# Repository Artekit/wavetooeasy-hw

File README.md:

# Artekit WaveTooEasy - Hardware files

This repository contains the Eagle files and mechanical drawings for the [Artekit WaveTooEasy](https://www.artekit.eu/products/devboards/wavetooeasy/) board.

## Links

* [WaveTooEasy product page](https://www.artekit.eu/products/devboards/wavetooeasy/)
* [WaveTooEasy manual](https://www.artekit.eu/doc/guides/wavetooeasy/)
* [WaveTooEasy - Library for Arduino](https://github.com/Artekit/Artekit_WaveTooEasy)
* [WaveTooEasy - Generic C library](https://github.com/Artekit/wavetooeasy-c-lib)

## Bugs report

You can report bugs here by creating a new issue or in the [Artekit forum](https://forum.artekit.eu/).

## License

Attribution-ShareAlike 3.0 Unported (CC BY-SA 3.0)

Copyright (c) 2021 Artekit Labs.

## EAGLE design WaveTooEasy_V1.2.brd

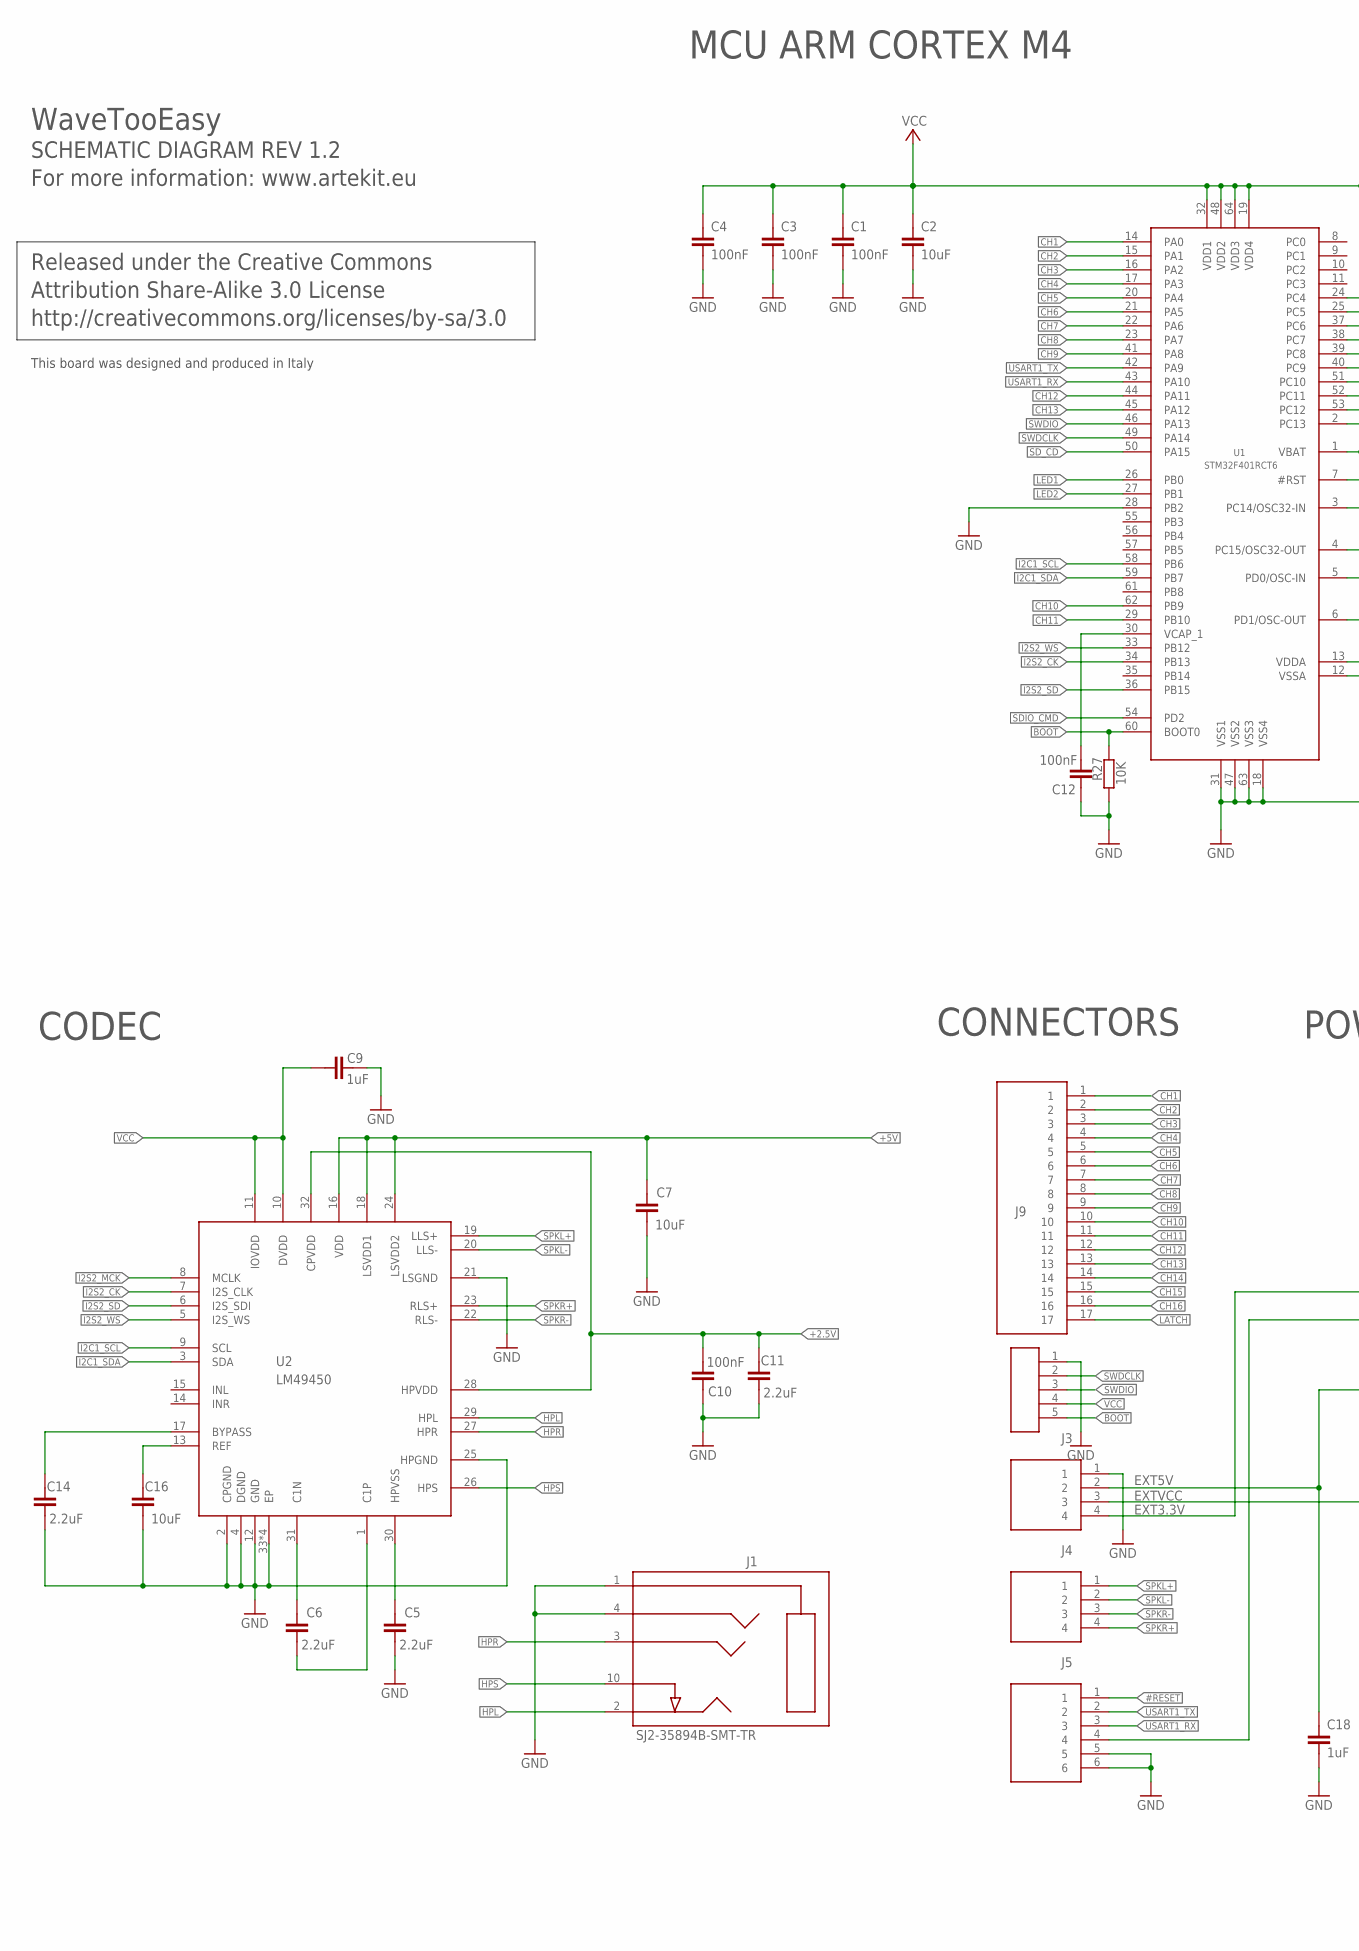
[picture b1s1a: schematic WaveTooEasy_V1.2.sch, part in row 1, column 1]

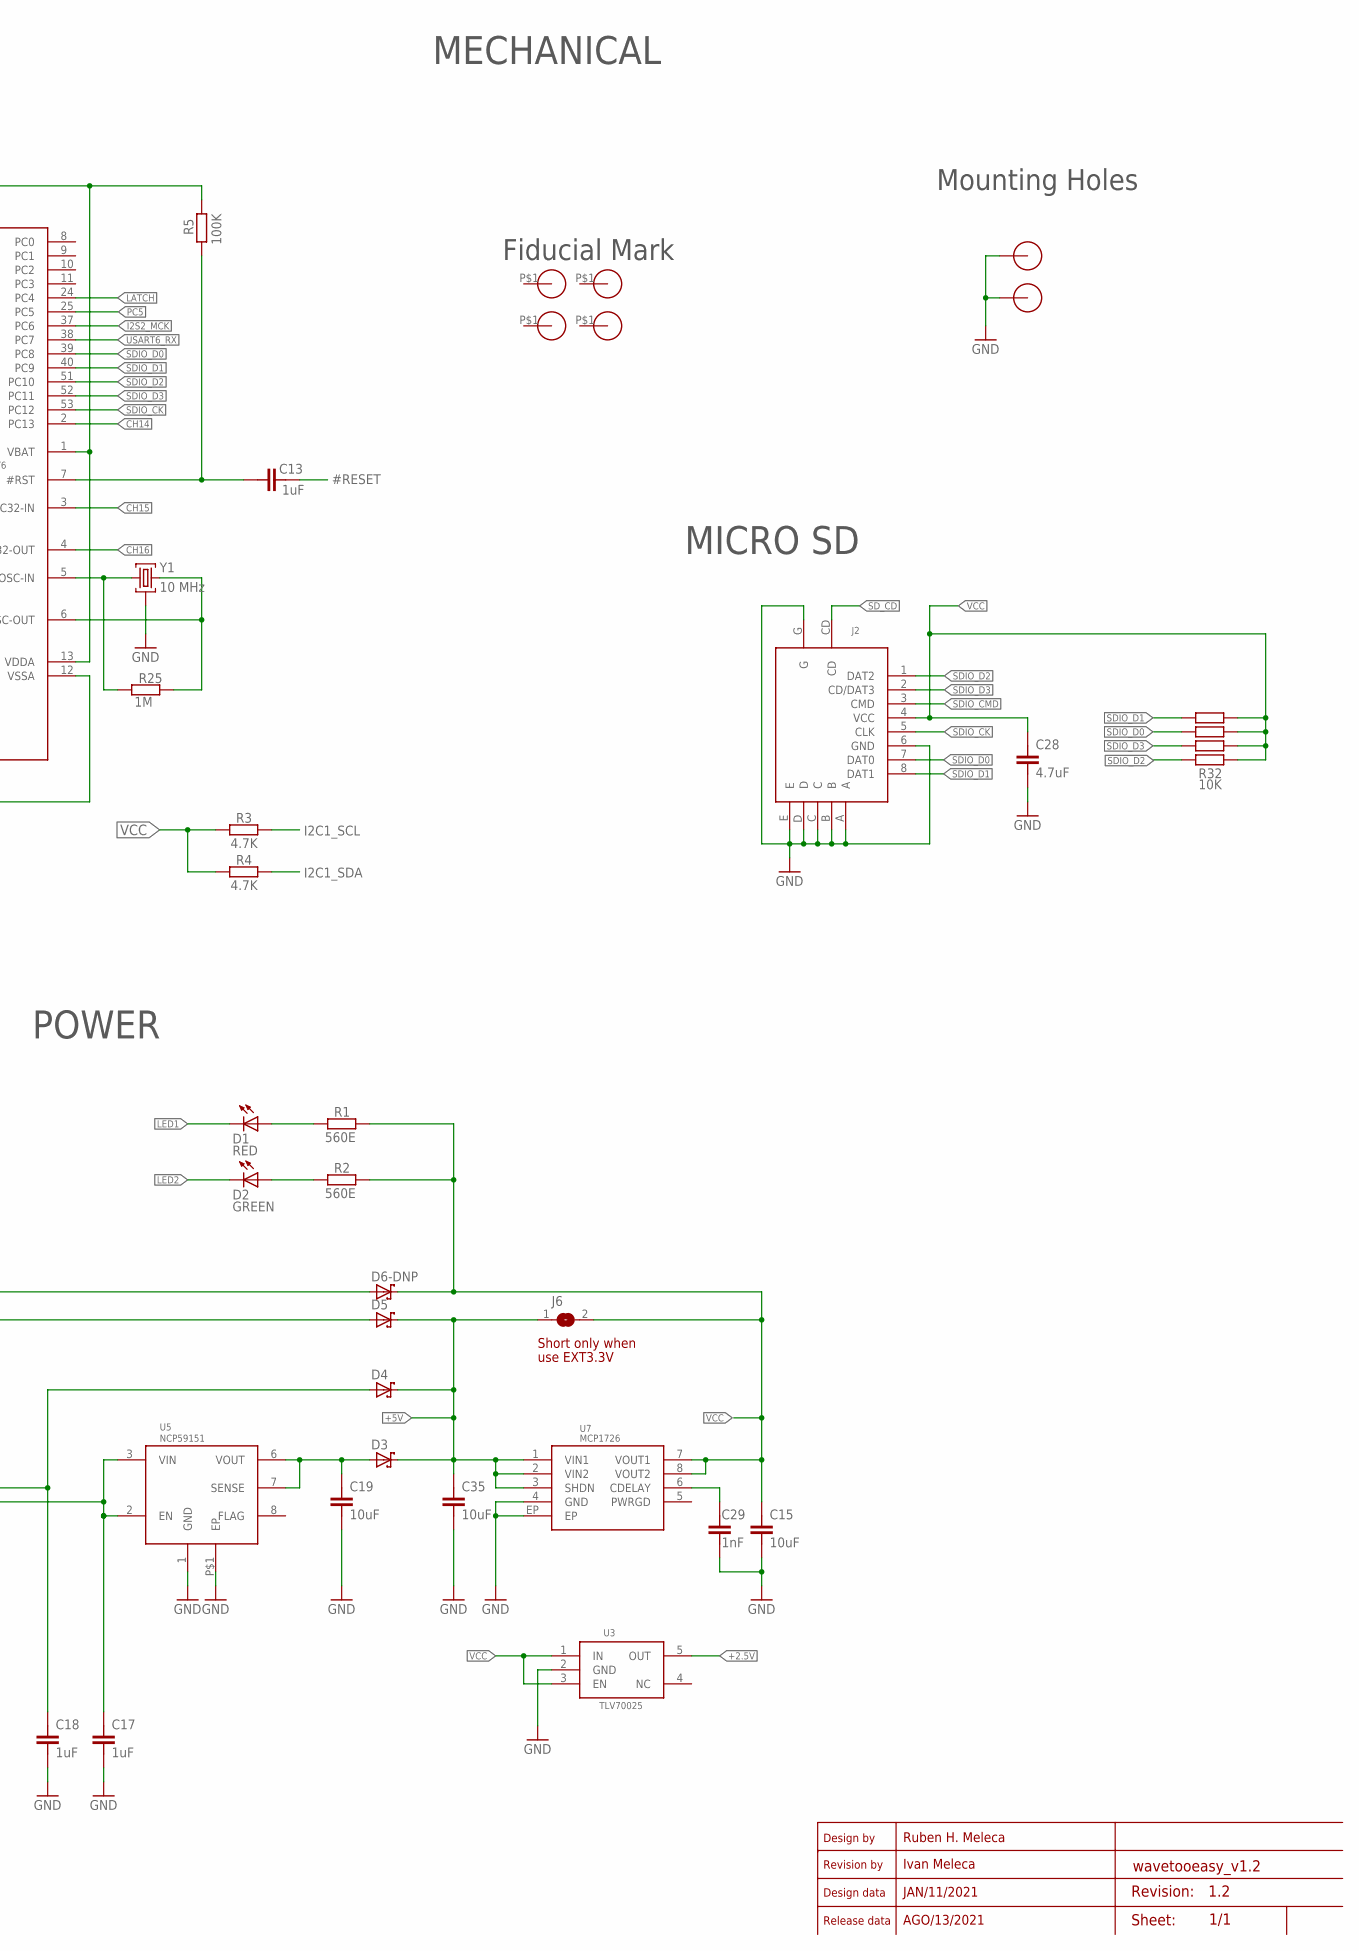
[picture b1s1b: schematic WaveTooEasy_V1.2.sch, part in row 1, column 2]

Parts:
C1, C3, C4, C10, C12: 100nF; C0402
C2, C7, C15, C16, C19, C35: 10uF; C0402
C5, C6, C11, C14: 2.2uF; C0402
C9, C13, C17, C18: 1uF; C0402
C28: 4.7uF; C0402
C29: 1nF; C0402
D1: RED; CHIPLED_0603
D2: GREEN; CHIPLED_0603
D3, D4, D5, D6-DNP: BAT60; SOD-323
J1: SJ2-35894B-SMT-TR
J2: MICRO-SD-CON-MOLEX-503182-0852
J3, J4: CON-PH-1X04-P01"2; PIN-HEADER-1X04-NODASH
J5: CON-PH-1X06-P0.1"1; PIN-HEADER-1X6-NODASH
J6: JUMPER-2
J9: CON-PH-1X17-P0.1; PIN-HEADER-1X17-NODASH
R1, R2: 560E; R0402
R3, R4: 4.7K; R0402
R5: 100K; R0402
R25: 1M; R0402
R27: 10K; R0402
R32: 10K; RES-ARRAY-0603
U1: STM32F401RCT6; LQFP64-10X10-P0.50; MPN STM32F401RCT6
U2: LM49450; QFN32-5X5-P0.50
U3: TLV70025; SOT363-5
U5: NCP59151; DFN8-4X4
U7: MCP1726; DFN8-3X3
U$1: CON-PH-1X05-P0.1"; PIN-HEADER-1X05-NODASH
U$3, U$4: HOLE-2MM-METALIZED
U$5, U$6, U$8, U$9: FIDUTIAL_1.2MM
Y1: 10 MHz; RESONATOR-MURATA-CSTCE-SERIES

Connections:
#RESET: C13.2, J5.1
+2.5V: C10.1, C11.1, U2.28 (HPVDD), U2.32 (CPVDD), U3.5 (OUT)
+5V: C7.1, C35.1, D3.C, D4.C, D5.C, J6.1, U2.16 (VDD), U2.18 (LSVDD1), U2.24 (LSVDD2), U7.1 (VIN1), U7.2 (VIN2), U7.3 (SHDN)
BOOT: R27.2, U1.60 (BOOT0), U$1.5
CH1: J9.1, U1.14 (PA0)
CH2: J9.2, U1.15 (PA1)
CH3: J9.3, U1.16 (PA2)
CH4: J9.4, U1.17 (PA3)
CH5: J9.5, U1.20 (PA4)
CH6: J9.6, U1.21 (PA5)
CH7: J9.7, U1.22 (PA6)
CH8: J9.8, U1.23 (PA7)
CH9: J9.9, U1.41 (PA8)
CH10: J9.10, U1.62 (PB9)
CH11: J9.11, U1.29 (PB10)
CH12: J9.12, U1.44 (PA11)
CH13: J9.13, U1.45 (PA12)
CH14: J9.14, U1.2 (PC13)
CH15: J9.15, U1.3 (PC14/OSC32-IN)
CH16: J9.16, U1.4 (PC15/OSC32-OUT)
EXT3.3V: D6-DNP.A, J3.4
EXT5V: C18.1, D4.A, J3.2
EXTVCC: C17.1, J3.3, U5.2 (EN), U5.3 (VIN)
GND: C1.2, C2.2, C3.2, C4.2, C5.2, C7.2, C9.2, C10.2, C11.2, C12.2, C14.2, C15.2, C16.2, C17.2, C18.2, C19.2, C28.2, C29.2, C35.2, J1.1, J1.4, J2.6 (GND), J2.A, J2.B, J2.C, J2.D, J2.E, J2.G, J3.1, J5.5, J5.6, R27.1, U1.12 (VSSA), U1.18 (VSS4), U1.28 (PB2), U1.31 (VSS1), U1.47 (VSS2), U1.63 (VSS3), U2.2 (CPGND), U2.4 (DGND), U2.12 (GND), U2.21 (LSGND), U2.25 (HPGND), U2.33 (EP), U2.34 (EP), U2.35 (EP), U2.36 (EP), U3.2 (GND), U5.1 (GND), U5.P$1 (EP), U7.4 (GND), U7.EP, U$1.1, U$3.1, U$4.1, Y1.2
HPL: J1.2, U2.29 (HPL)
HPR: J1.3, U2.27 (HPR)
HPS: J1.10, U2.26 (HPS)
I2C1_SCL: R3.1, U1.58 (PB6), U2.9 (SCL)
I2C1_SDA: R4.1, U1.59 (PB7), U2.3 (SDA)
I2S2_CK: U1.34 (PB13), U2.7 (I2S_CLK)
I2S2_MCK: U1.37 (PC6), U2.8 (MCLK)
I2S2_SD: U1.36 (PB15), U2.6 (I2S_SDI)
I2S2_WS: U1.33 (PB12), U2.5 (I2S_WS)
LATCH: J9.17, U1.24 (PC4)
LED1: D1.C, U1.26 (PB0)
LED2: D2.C, U1.27 (PB1)
unnamed: C19.1, D3.A, U5.6 (VOUT), U5.7 (SENSE)
unnamed: C6.1, U2.31 (C1N)
unnamed: C6.2, U2.1 (C1P)
unnamed: C5.1, U2.30 (HPVSS)
unnamed: C16.1, U2.13 (REF)
unnamed: C14.1, U2.17 (BYPASS)
unnamed: D5.A, J5.4
unnamed: C13.1, R5.1, U1.7 (#RST)
unnamed: R25.1, U1.5 (PD0/OSC-IN), Y1.1
unnamed: R25.2, U1.6 (PD1/OSC-OUT), Y1.3
unnamed: D2.A, R2.2
unnamed: D1.A, R1.2
unnamed: C29.1, U7.6 (CDELAY)
unnamed: C12.1, U1.30 (VCAP_1)
PC5: U1.25 (PC5)
SDIO_CK: J2.5 (CLK), U1.53 (PC12)
SDIO_CMD: J2.3 (CMD), U1.54 (PD2)
SDIO_D0: J2.7 (DAT0), R32.3, U1.39 (PC8)
SDIO_D1: J2.8 (DAT1), R32.1, U1.40 (PC9)
SDIO_D2: J2.1 (DAT2), R32.7, U1.51 (PC10)
SDIO_D3: J2.2 (CD/DAT3), R32.5, U1.52 (PC11)
SD_CD: J2.CD, U1.50 (PA15)
SPKL+: J4.1, U2.19 (LLS+)
SPKL-: J4.2, U2.20 (LLS-)
SPKR+: J4.4, U2.23 (RLS+)
SPKR-: J4.3, U2.22 (RLS-)
SWDCLK: U1.49 (PA14), U$1.2
SWDIO: U1.46 (PA13), U$1.3
USART1_RX: J5.3, U1.43 (PA10)
USART1_TX: J5.2, U1.42 (PA9)
USART6_RX: U1.38 (PC7)
VCC: C1.1, C2.1, C3.1, C4.1, C9.1, C15.1, C28.1, D6-DNP.C, J2.4 (VCC), J6.2, R1.1, R2.1, R3.2, R4.2, R5.2, R32.2, R32.4, R32.6, R32.8, U1.1 (VBAT), U1.13 (VDDA), U1.19 (VDD4), U1.32 (VDD1), U1.48 (VDD2), U1.64 (VDD3), U2.10 (DVDD), U2.11 (IOVDD), U3.1 (IN), U3.3 (EN), U7.7 (VOUT1), U7.8 (VOUT2), U$1.4

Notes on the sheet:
POWER
CONNECTORS
MCU ARM CORTEX M4
MICRO SD
MECHANICAL
Released under the Creative Commons
Attribution Share-Alike 3.0 License
http://creativecommons.org/licenses/by-sa/3.0
This board was designed and produced in Italy
Fiducial Mark
Mounting Holes
CODEC
Sheet:
Design by
Revision by
Design data
Release data
Revision:
Ruben H. Meleca
Ivan Meleca
JAN/11/2021
AGO/13/2021
1.2
Short only when
use EXT3.3V
WaveTooEasy
SCHEMATIC DIAGRAM REV 1.2
For more information: www.artekit.eu

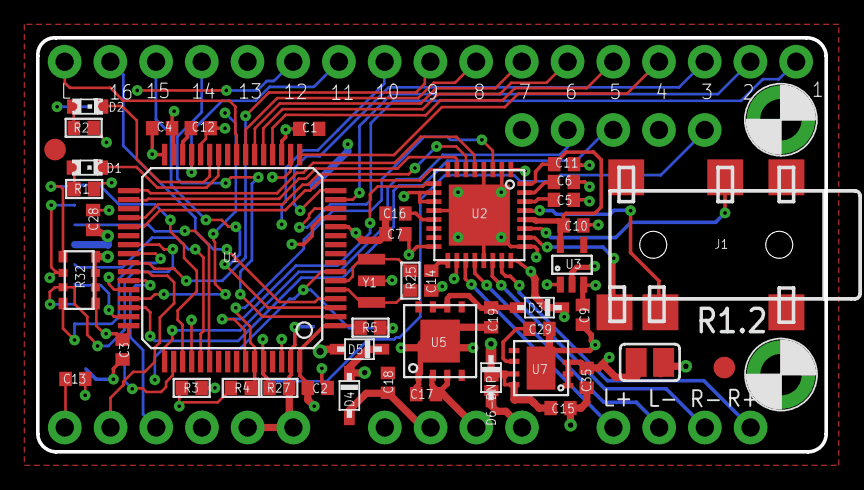
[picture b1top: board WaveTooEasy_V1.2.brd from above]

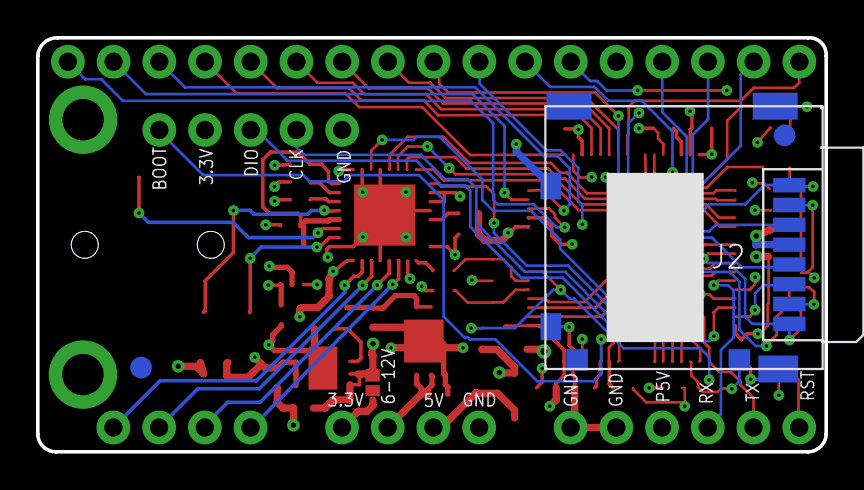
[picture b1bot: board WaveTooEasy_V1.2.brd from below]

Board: 2 copper layers, 43.8 x 23.0 mm, 55 parts (3 on the bottom side), 66 nets.
